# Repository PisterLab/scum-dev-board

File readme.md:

feedback page: https://crystalfree.atlassian.net/wiki/x/AQDGJg

Currently there are three versions of the dev board in this folder
- scum3c_devboard is a KiCad model of the currently in-use board as of October 12th 2020. It might be not 100% accurate to the original: https://github.com/PisterLab/scum-dev-board/blob/master/SCM3C_PCB.pdf
- mccoy is a small 1.675 in X 1.35 in board. It has GPIO pins, an IMU, and battery power
- scum3c_devboard_large is a larger board, supposed to replace the currenly in-use board

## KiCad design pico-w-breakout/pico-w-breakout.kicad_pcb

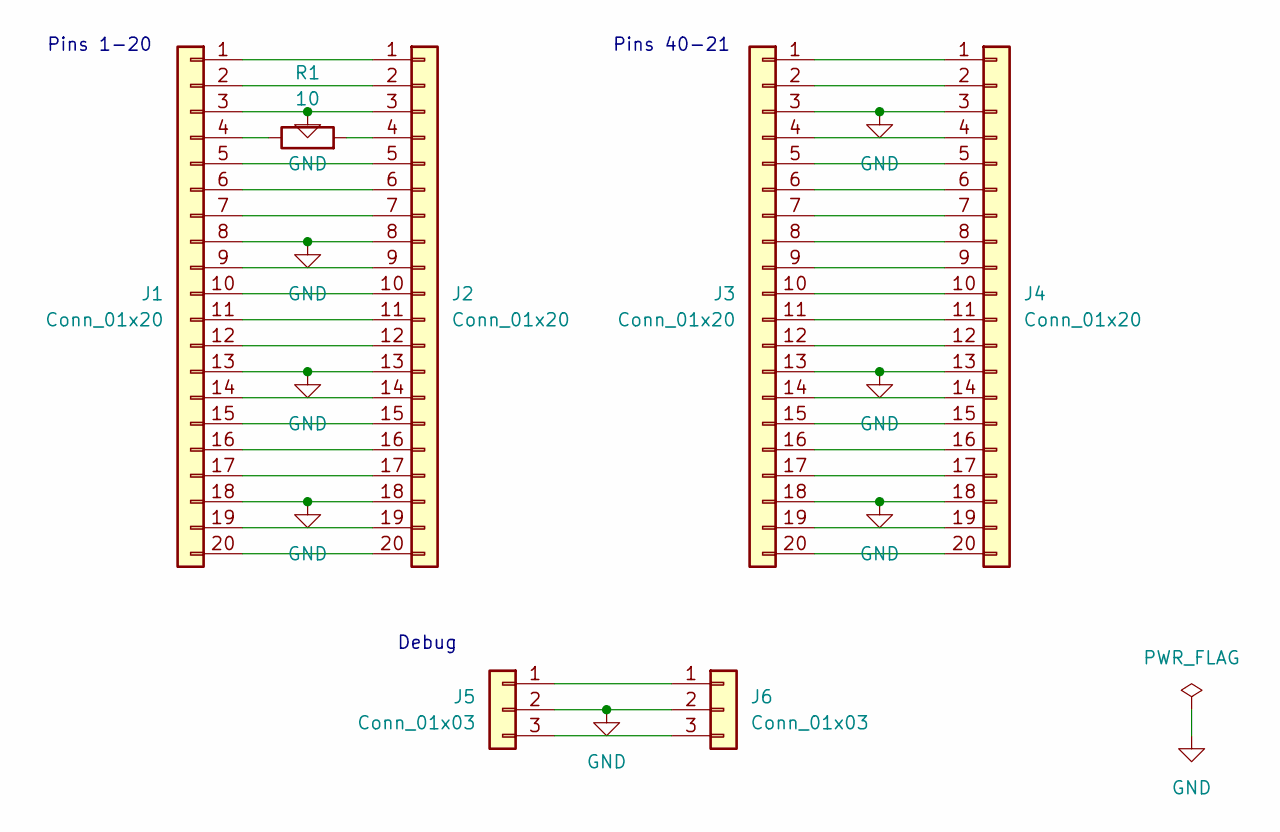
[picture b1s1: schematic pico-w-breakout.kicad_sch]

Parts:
J1, J4: Conn_01x20; PinHeader_1x20_P2.54mm_Vertical
J2, J3: Conn_01x20; PinSocket_1x20_P2.54mm_Vertical
J5: Conn_01x03; PinHeader_1x03_P2.54mm_Vertical
J6: Conn_01x03; PinSocket_1x03_P2.54mm_Vertical
R1: 10; R_0603_1608Metric

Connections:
GND: J1.3, J1.8, J1.13, J1.18, J2.3, J2.8, J2.13, J2.18, J3.3, J3.13, J3.18, J4.3, J4.13, J4.18, J5.2, J6.2
unnamed: J1.1, J2.1
unnamed: J1.2, J2.2
unnamed: J1.4, R1.1
unnamed: J1.5, J2.5
unnamed: J1.6, J2.6
unnamed: J1.7, J2.7
unnamed: J1.9, J2.9
unnamed: J1.10, J2.10
unnamed: J1.11, J2.11
unnamed: J1.12, J2.12
unnamed: J1.14, J2.14
unnamed: J1.15, J2.15
unnamed: J1.16, J2.16
unnamed: J1.17, J2.17
unnamed: J1.19, J2.19
unnamed: J1.20, J2.20
unnamed: J2.4, R1.2
unnamed: J3.1, J4.1
unnamed: J3.2, J4.2
unnamed: J3.4, J4.4
unnamed: J3.5, J4.5
unnamed: J3.6, J4.6
unnamed: J3.7, J4.7
unnamed: J3.8, J4.8
unnamed: J3.9, J4.9
unnamed: J3.10, J4.10
unnamed: J3.11, J4.11
unnamed: J3.12, J4.12
unnamed: J3.14, J4.14
unnamed: J3.15, J4.15
unnamed: J3.16, J4.16
unnamed: J3.17, J4.17
unnamed: J3.19, J4.19
unnamed: J3.20, J4.20
unnamed: J5.1, J6.1
unnamed: J5.3, J6.3

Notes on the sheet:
Pins 40-21
Debug
Pins 1-20

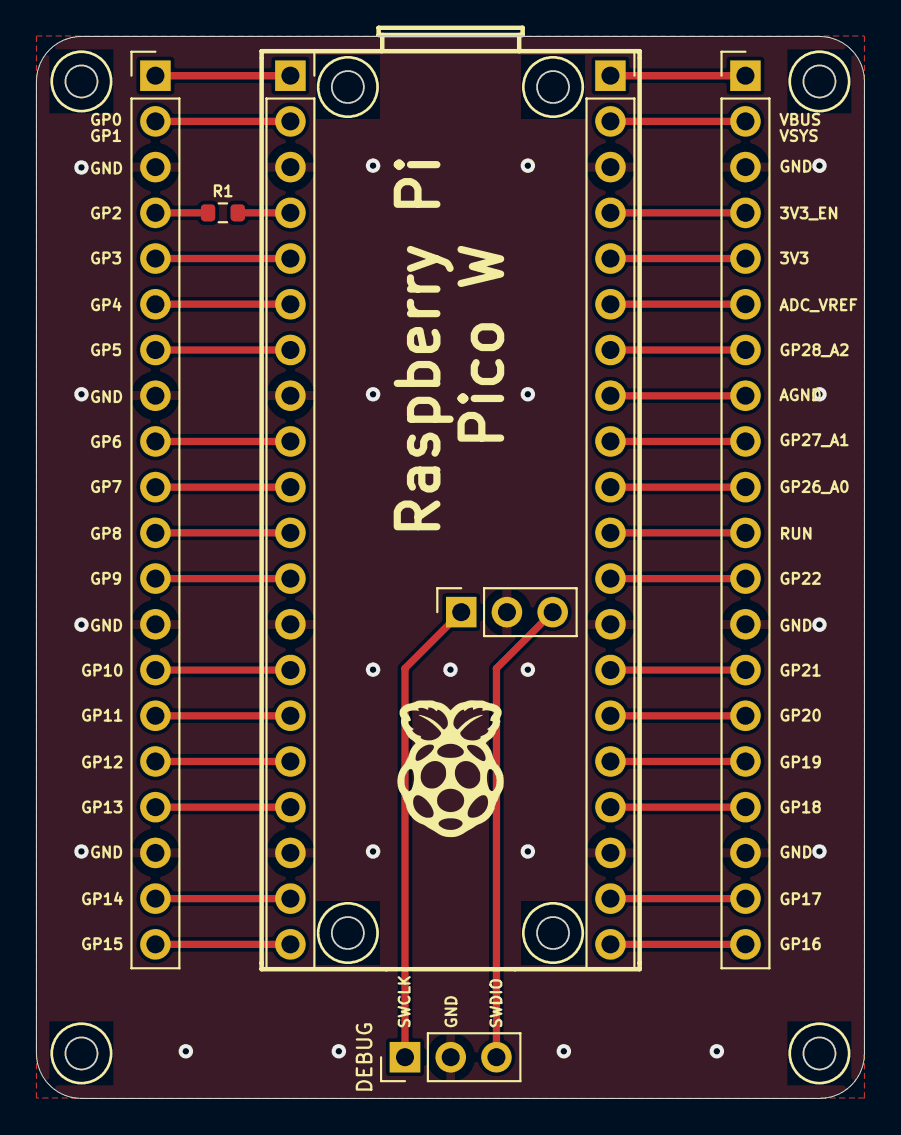
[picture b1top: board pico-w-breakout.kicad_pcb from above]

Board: 2 copper layers, 46.0 x 59.0 mm, 7 parts (0 on the bottom side), 37 nets.

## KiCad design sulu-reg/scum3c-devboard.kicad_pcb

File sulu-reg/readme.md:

# Changelog

### Update 2021.11.23
- Moved GND on 1x10 to match with nRF P4 in reverse orientation

| nRF pin | Sulu pin        |
|---------|-----------------|
| P1.10   | VBAT            |
| P1.11   | NRF_VDDD / HI-Z |
| P1.12   | NRF_GND / HI-Z  |
| P1.13   | HARD_RESET      |
| P1.14   | 3WB_DATA        |
| P1.15   | 3WB_ENB         |
| GND     | GND             |
| P0.02   | 3WB_CLK         |
| P0.26   | RsRx            |
| P0.27   | RsTx            |

### Update 2021.11.19
- Rdded orientation dots for DC-DC converters and IMU
- Replaced 2x5 header with 1x10 header for nRF interface.

### Update 2021.11.04
Replaced DC-DC converter inductor and capacitor footprints to fit with recommended passives from datasheet https://www.ablic.com/en/doc/datasheet/switching_regulator/S85S1A_E.pdf

# images

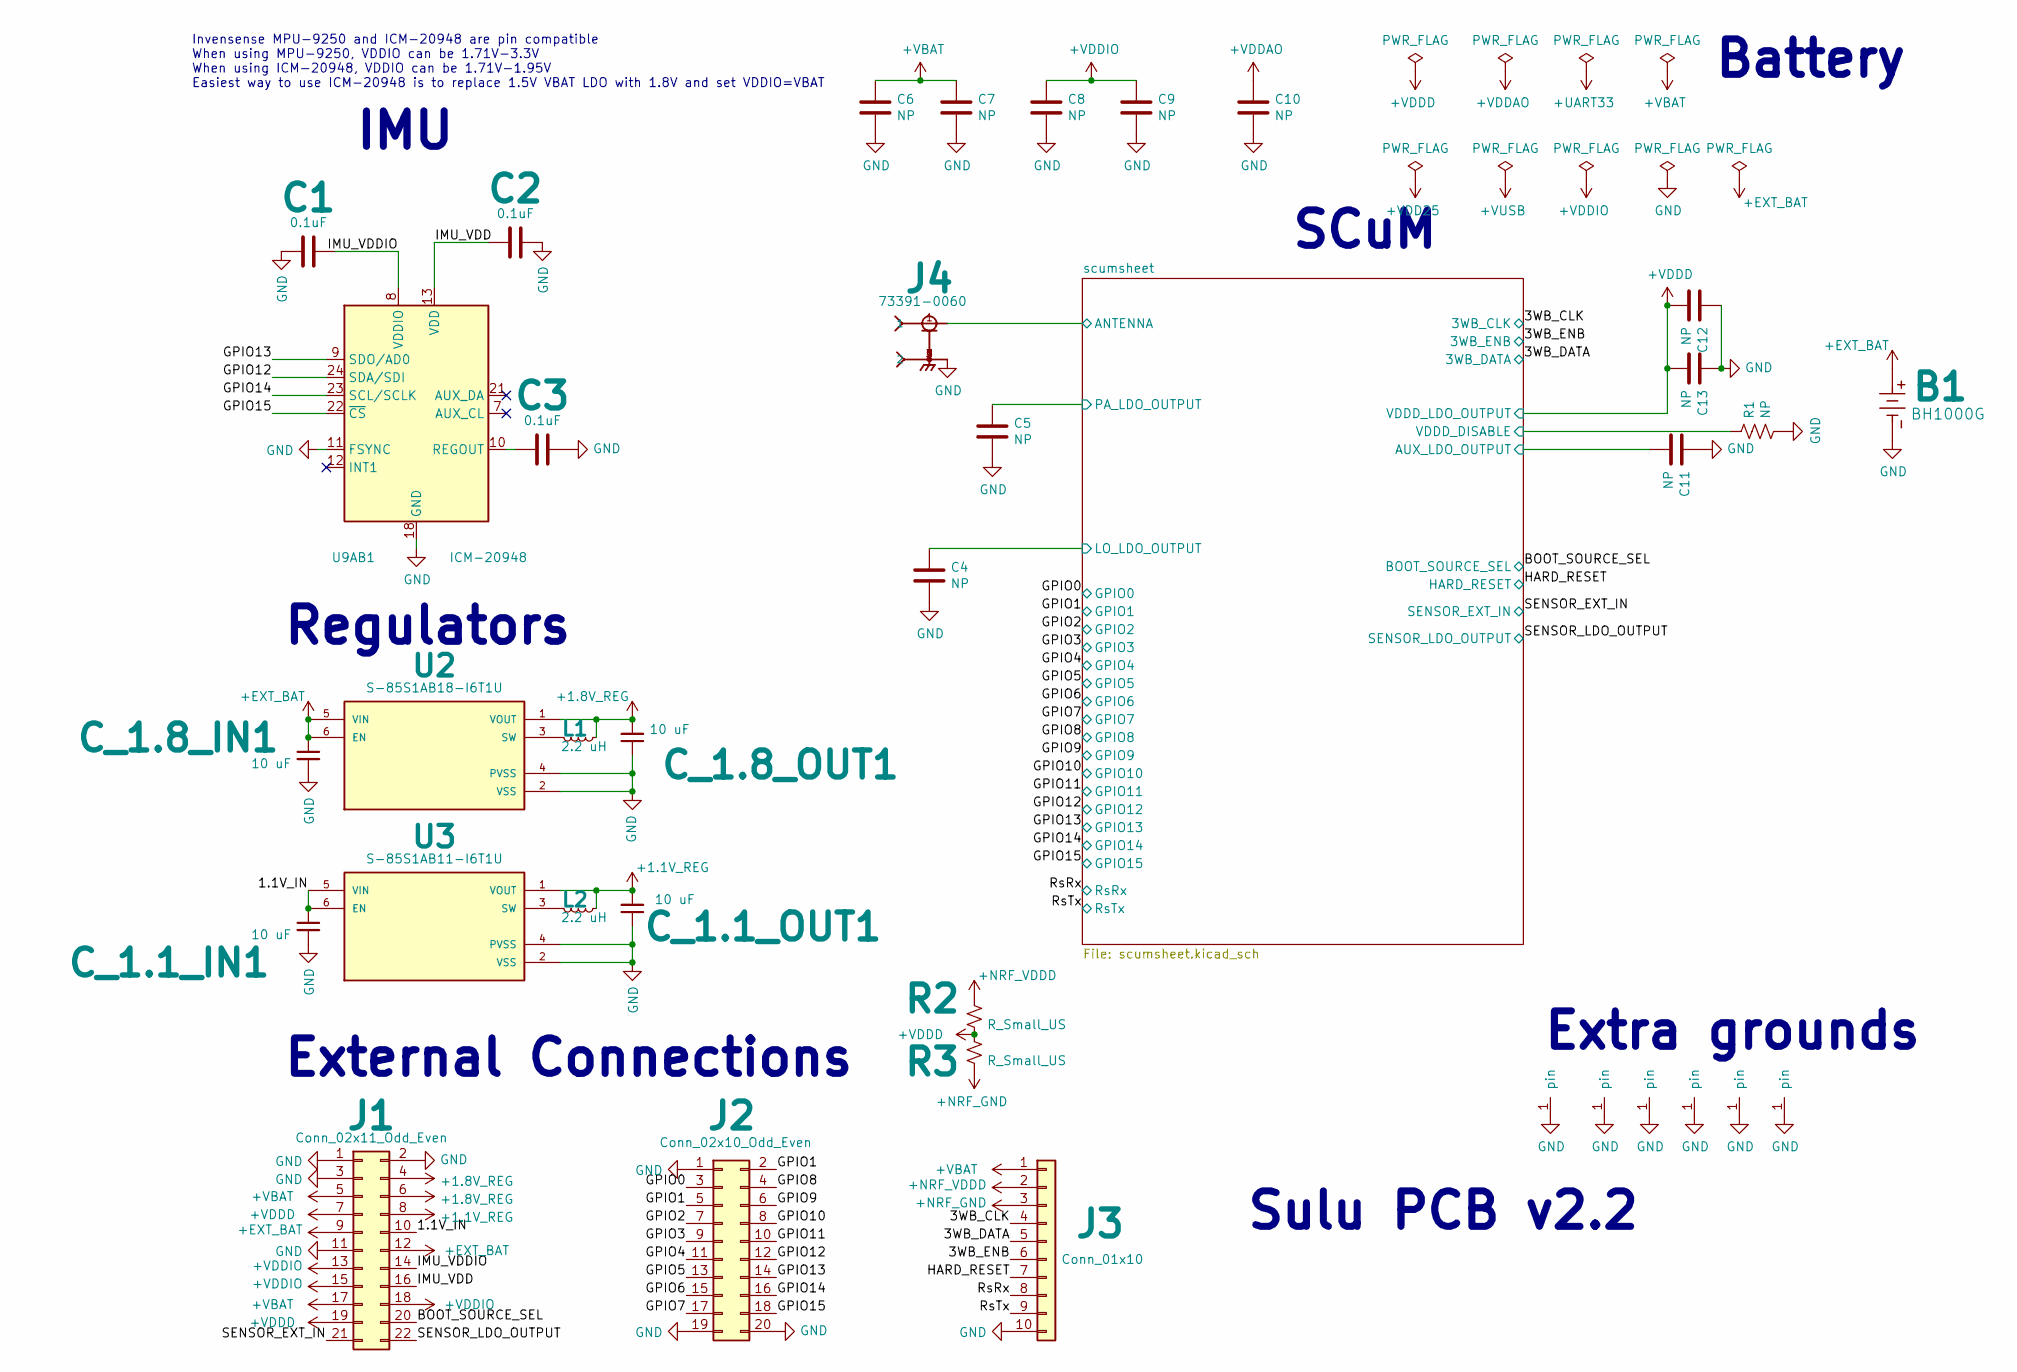
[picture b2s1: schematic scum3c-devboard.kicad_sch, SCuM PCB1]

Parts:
B1: BH1000G
C1, C2, C3: 0.1uF; C_0402_1005Metric
C4, C5, C6, C7, C8, C9, C10, C11, C12, C13: NP; C_0402_1005Metric
C_1.1_IN1, C_1.1_OUT1, C_1.8_IN1, C_1.8_OUT1: 10 uF; C_0402_1005Metric
GND1, GND2, GND3, GND4, GND5, GND6: through_hole
J1: Conn_02x11_Odd_Even; PinHeader_2x11_P2.54mm_Vertical
J2: Conn_02x10_Odd_Even; PinHeader_2x10_P2.54mm_Vertical
J3: Conn_01x10; PinHeader_1x10_P2.54mm_Vertical
J4: 73391-0060; MOLEX_73391-0060
L1, L2: 2.2 uH; L_Wuerth_MAPI-2010
R1: NP; R_0402_1005Metric
R2, R3: R_Small_US; R_0402_1005Metric
U2: S-85S1AB18-I6T1U; SOFL50P180X50-6N; PARTREV 1.4_00
U3: S-85S1AB11-I6T1U; SOFL50P180X50-6N; PARTREV 1.4_00
U9AB1: ICM-20948; InvenSense_QFN-24_3x3mm_P0.4mm

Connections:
+1.1V_REG: C_1.1_OUT1.2, J1.8, L2.1, U3.1 (VOUT)
+1.8V_REG: C_1.8_OUT1.2, J1.4, J1.6, L1.1, U2.1 (VOUT)
+EXT_BAT: B1.2, C_1.8_IN1.1, J1.9, J1.12, U2.5 (VIN), U2.6 (EN)
+NRF_GND: J3.3, R3.2
+NRF_VDDD: J3.2, R2.1
+VBAT: C6.1, C7.1, J1.5, J1.17, J3.1; also elsewhere on the board
+VDDAO: C10.1; also elsewhere on the board
+VDDD: C12.2, C13.2, J1.7, J1.19, R2.2, R3.1; also elsewhere on the board
+VDDIO: C8.1, C9.1, J1.13, J1.15, J1.18; also elsewhere on the board
/1.1V_IN: C_1.1_IN1.1, J1.10, U3.5 (VIN), U3.6 (EN)
/3WB_CLK: J3.4; also elsewhere on the board
/3WB_DATA: J3.5; also elsewhere on the board
/3WB_ENB: J3.6; also elsewhere on the board
/BOOT_SOURCE_SEL: J1.20; also elsewhere on the board
/GPIO0: J2.3; also elsewhere on the board
/GPIO1: J2.2, J2.5; also elsewhere on the board
/GPIO2: J2.7; also elsewhere on the board
/GPIO3: J2.9; also elsewhere on the board
/GPIO4: J2.11; also elsewhere on the board
/GPIO5: J2.13; also elsewhere on the board
/GPIO6: J2.15; also elsewhere on the board
/GPIO7: J2.17; also elsewhere on the board
/GPIO8: J2.4; also elsewhere on the board
/GPIO9: J2.6; also elsewhere on the board
/GPIO10: J2.8; also elsewhere on the board
/GPIO11: J2.10; also elsewhere on the board
/GPIO12: J2.12, U9AB1.24 (SDA/SDI); also elsewhere on the board
/GPIO13: J2.14, U9AB1.9 (SDO/AD0); also elsewhere on the board
/GPIO14: J2.16, U9AB1.23 (SCL/SCLK); also elsewhere on the board
/GPIO15: J2.18, U9AB1.22 (~CS); also elsewhere on the board
/HARD_RESET: J3.7; also elsewhere on the board
/IMU_VDD: C2.1, J1.16, U9AB1.13 (VDD)
/IMU_VDDIO: C1.1, J1.14, U9AB1.8 (VDDIO)
/RsRx: J3.8; also elsewhere on the board
/RsTx: J3.9; also elsewhere on the board
/SENSOR_EXT_IN: J1.21; also elsewhere on the board
/SENSOR_LDO_OUTPUT: J1.22; also elsewhere on the board
/scumsheet/ANTENNA: J4.1; also elsewhere on the board
/scumsheet/AUX_LDO_OUTPUT: C11.2; also elsewhere on the board
/scumsheet/LO_LDO_OUTPUT: C4.1; also elsewhere on the board
/scumsheet/PA_LDO_OUTPUT: C5.1; also elsewhere on the board
/scumsheet/VDDD_DISABLE: R1.1; also elsewhere on the board
GND: B1.1, C1.2, C2.2, C3.2, C4.2, C5.2, C6.2, C7.2, C8.2, C9.2, C10.2, C11.1, C12.1, C13.1, C_1.1_IN1.2, C_1.1_OUT1.1, C_1.8_IN1.2, C_1.8_OUT1.1, GND1.1 (pin), GND2.1 (pin), GND3.1 (pin), GND4.1 (pin), GND5.1 (pin), GND6.1 (pin), J1.1, J1.2, J1.3, J1.11, J2.1, J2.19, J2.20, J3.10, J4.2, J4.3 (2), J4.4 (2), J4.5 (2), R1.2, U2.2 (VSS), U2.4 (PVSS), U3.2 (VSS), U3.4 (PVSS), U9AB1.11 (FSYNC), U9AB1.18 (GND), U9AB1.20 (GND); also elsewhere on the board
unnamed: L1.2, U2.3 (SW)
unnamed: L2.2, U3.3 (SW)
unnamed: C3.1, U9AB1.10 (REGOUT)

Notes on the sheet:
SCuM
Extra grounds
Sulu PCB v2.2
Invensense MPU-9250 and ICM-20948 are pin compatible When using MPU-9250, VDDIO can be 1.71V-3.3V When using ICM-20948, VDDIO can be 1.71V-1.95V Easiest way to use ICM-20948 is to replace 1.5V VBAT LDO with 1.8V and set VDDIO=VBAT
External Connections
Regulators
Battery
IMU

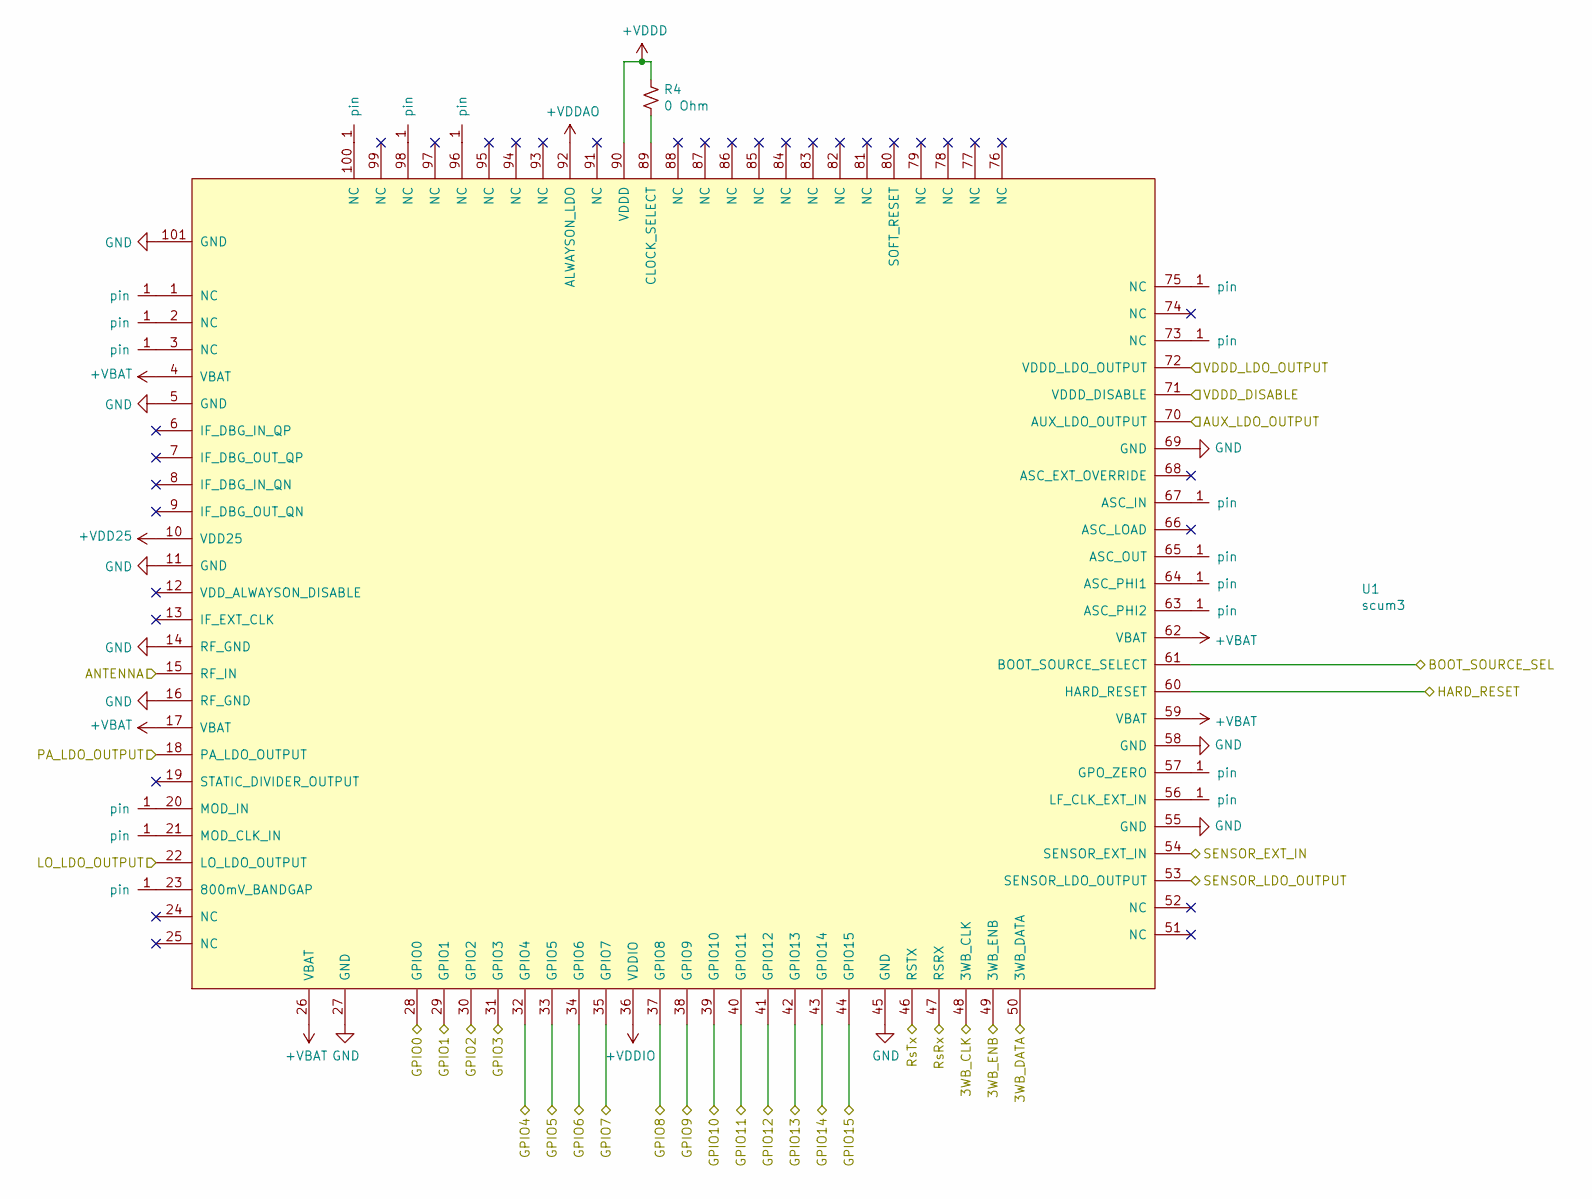
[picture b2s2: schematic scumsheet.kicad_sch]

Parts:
J5, J6, J7, J8, J9, J10, J11, J12, J13, J14, J15, J16, J17, J18, J19, J20, J21: through_hole
R4: 0 Ohm; R_0402_1005Metric
U1: scum3; QFN-100_EP_12x12_Pitch0.4mm_Margin0.25mm

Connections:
+VBAT: U1.4 (VBAT), U1.17 (VBAT), U1.26 (VBAT), U1.59 (VBAT), U1.62 (VBAT); also elsewhere on the board
+VDD25: U1.10 (VDD25)
+VDDAO: U1.92 (ALWAYSON_LDO); also elsewhere on the board
+VDDD: R4.1, U1.72 (VDDD_LDO_OUTPUT), U1.90 (VDDD); also elsewhere on the board
+VDDIO: U1.36 (VDDIO); also elsewhere on the board
/3WB_CLK: U1.48 (3WB_CLK); also elsewhere on the board
/3WB_DATA: U1.50 (3WB_DATA); also elsewhere on the board
/3WB_ENB: U1.49 (3WB_ENB); also elsewhere on the board
/BOOT_SOURCE_SEL: U1.61 (BOOT_SOURCE_SELECT); also elsewhere on the board
/GPIO0: U1.28 (GPIO0); also elsewhere on the board
/GPIO1: U1.29 (GPIO1); also elsewhere on the board
/GPIO2: U1.30 (GPIO2); also elsewhere on the board
/GPIO3: U1.31 (GPIO3); also elsewhere on the board
/GPIO4: U1.32 (GPIO4); also elsewhere on the board
/GPIO5: U1.33 (GPIO5); also elsewhere on the board
/GPIO6: U1.34 (GPIO6); also elsewhere on the board
/GPIO7: U1.35 (GPIO7); also elsewhere on the board
/GPIO8: U1.37 (GPIO8); also elsewhere on the board
/GPIO9: U1.38 (GPIO9); also elsewhere on the board
/GPIO10: U1.39 (GPIO10); also elsewhere on the board
/GPIO11: U1.40 (GPIO11); also elsewhere on the board
/GPIO12: U1.41 (GPIO12); also elsewhere on the board
/GPIO13: U1.42 (GPIO13); also elsewhere on the board
/GPIO14: U1.43 (GPIO14); also elsewhere on the board
/GPIO15: U1.44 (GPIO15); also elsewhere on the board
/HARD_RESET: U1.60 (HARD_RESET); also elsewhere on the board
/RsRx: U1.47 (RSRX); also elsewhere on the board
/RsTx: U1.46 (RSTX); also elsewhere on the board
/SENSOR_EXT_IN: U1.54 (SENSOR_EXT_IN); also elsewhere on the board
/SENSOR_LDO_OUTPUT: U1.53 (SENSOR_LDO_OUTPUT); also elsewhere on the board
/scumsheet/ANTENNA: U1.15 (RF_IN); also elsewhere on the board
/scumsheet/AUX_LDO_OUTPUT: U1.70 (AUX_LDO_OUTPUT); also elsewhere on the board
/scumsheet/LO_LDO_OUTPUT: U1.22 (LO_LDO_OUTPUT); also elsewhere on the board
/scumsheet/PA_LDO_OUTPUT: U1.18 (PA_LDO_OUTPUT); also elsewhere on the board
/scumsheet/VDDD_DISABLE: U1.71 (VDDD_DISABLE); also elsewhere on the board
GND: U1.5 (GND), U1.11 (GND), U1.14 (RF_GND), U1.16 (RF_GND), U1.27 (GND), U1.45 (GND), U1.55 (GND), U1.58 (GND), U1.69 (GND), U1.101 (GND); also elsewhere on the board
unnamed: J5.1 (pin), U1.73 (NC)
unnamed: J6.1 (pin), U1.1 (NC)
unnamed: J7.1 (pin), U1.2 (NC)
unnamed: J8.1 (pin), U1.3 (NC)
unnamed: J9.1 (pin), U1.63 (ASC_PHI2)
unnamed: J10.1 (pin), U1.64 (ASC_PHI1)
unnamed: J11.1 (pin), U1.20 (MOD_IN)
unnamed: J12.1 (pin), U1.21 (MOD_CLK_IN)
unnamed: J13.1 (pin), U1.23 (800mV_BANDGAP)
unnamed: J14.1 (pin), U1.100 (NC)
unnamed: J15.1 (pin), U1.67 (ASC_IN)
unnamed: J16.1 (pin), U1.65 (ASC_OUT)
unnamed: J17.1 (pin), U1.56 (LF_CLK_EXT_IN)
unnamed: J18.1 (pin), U1.98 (NC)
unnamed: J19.1 (pin), U1.96 (NC)
unnamed: J20.1 (pin), U1.75 (NC)
unnamed: J21.1 (pin), U1.57 (GPO_ZERO)
unnamed: R4.2, U1.89 (CLOCK_SELECT)

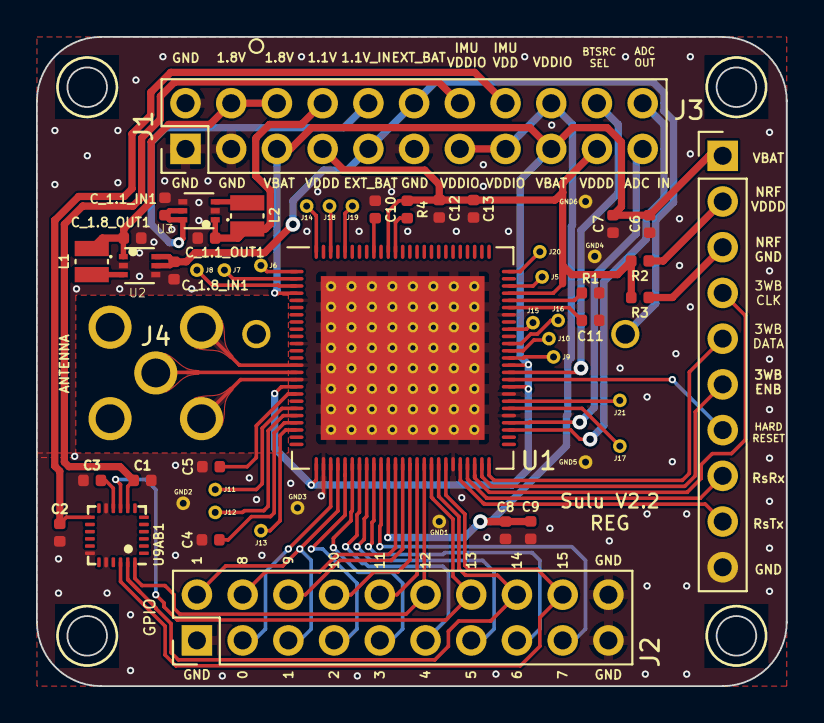
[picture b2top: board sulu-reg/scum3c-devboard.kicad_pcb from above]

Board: 2 copper layers, 41.7 x 36.1 mm, 55 parts (1 on the bottom side), 64 nets.

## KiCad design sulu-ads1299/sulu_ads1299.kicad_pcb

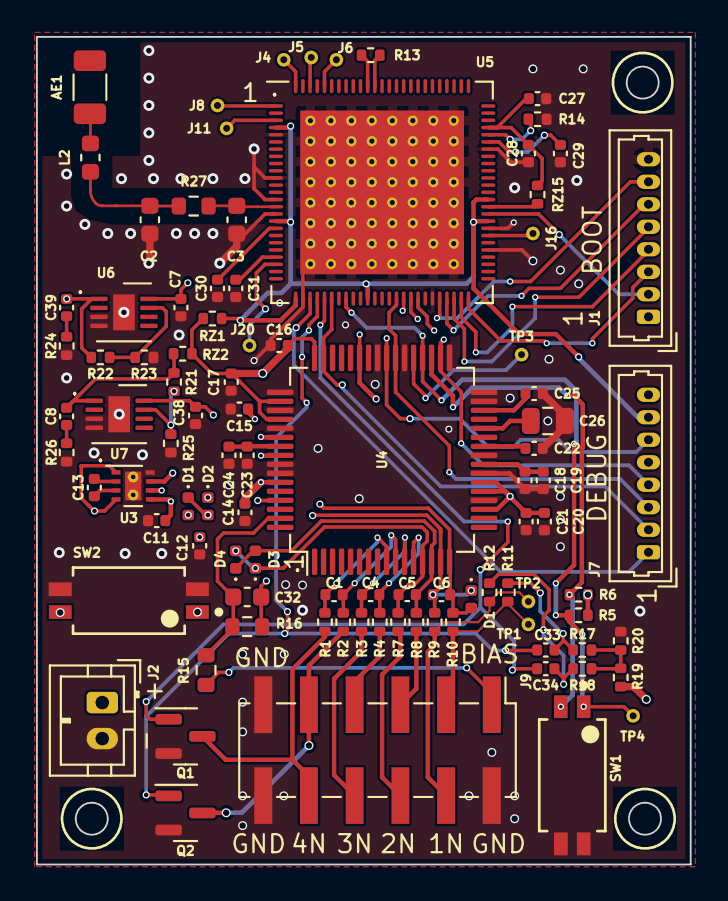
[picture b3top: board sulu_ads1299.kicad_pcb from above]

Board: 6 copper layers, 36.3 x 46.0 mm, 95 parts (1 on the bottom side), 75 nets.

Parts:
AE1: RFANT3216120A5T; C_1206_3216Metric
C1, C4, C5, C6, C33, C34: 3.3 uF; C_0402_1005Metric
C2: 0.5 pF; C_0603_1608Metric
C3: NP; C_0603_1608Metric
C7, C13, C14, C17, C20, C22, C23, C25, C38: 1 uF; C_0402_1005Metric
C8, C39: 4.7 uF; C_0402_1005Metric
C11, C12, C19: 10 uF; C_0402_1005Metric
C15, C16, C18, C21, C24: 0.1 uF; C_0402_1005Metric
C26: 100 uF; C_0805_2012Metric
C27, C28, C29, C30, C31: NP; C_0402_1005Metric
C32: 0.01uF; C_0603_1608Metric
D1, D1#2, D2, D3, D4: GDZ5V1LP3-7; D_0402_1005Metric
J1, J7: Conn_01x08; Molex_PicoBlade_53047-0810_1x08_P1.25mm_Vertical
J2: Conn_01x02; JST_PH_B2B-PH-K_1x02_P2.00mm_Vertical
J4, J5, J6, J8, J11, J16, J20: through_hole
J9: Conn_02x06_Odd_Even; PinHeader_2x06_P2.54mm_Vertical_SMD
L2: 6.7 nH; L_0603_1608Metric
Q1, Q2: BSS138; SOT-23
R1, R2, R3, R4, R7, R8, R9, R10: 200; R_0402_1005Metric
R5, R6: 10K; R_0402_1005Metric
R11, R12: 0; R_0402_1005Metric
R13: 0 Ohm; R_0402_1005Metric
R14: NP; R_0402_1005Metric
R15: 4.99K; R_0603_1608Metric
R16: 392K; R_0603_1608Metric
R17, R18, R19, R20, R23, R25: 100K; R_0402_1005Metric
R21, R22: 46K; R_0402_1005Metric
R24, R26: 1; R_0402_1005Metric
R27: 0; R_0603_1608Metric
RZ1, RZ15: 0 Ohm; R_0402_1005Metric
RZ2: NP; R_0402_1005Metric
SW1, SW2: SW_DIP_x02; CK_Components-TDA02H0SB1-MFG
TP1, TP2, TP3, TP4: TestPoint; through_hole
U3: LM2775DSG; WSON-8-1EP_2x2mm_P0.5mm_EP0.9x1.6mm_ThermalVias
U4: ADS1299_TQFP-64; TQFP-64_10x10mm_P0.5mm
U5: scum3; QFN-100_EP_12x12_Pitch0.4mm_Margin0.25mm
U6, U7: LP2951-5.0_WSON; WSON-8-1EP_3x3mm_P0.5mm_EP1.2x2mm

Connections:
+5V_REG: C12.1, C14.1, C15.1, C20.1, C21.1, R19.1, U3.6 (VOUT), U4.19 (AVDD), U4.21 (AVDD), U4.22 (AVDD), U4.54 (AVDD1), U4.56 (AVDD), U4.59 (AVDD)
+EXT_BAT: J1.1, J2.1, SW2.1
/3WB_CLK: J1.5, U5.48 (3WB_CLK)
/3WB_DATA: J1.3, U5.50 (3WB_DATA)
/3WB_ENB: J1.4, U5.49 (3WB_ENB)
/+1.8V_ADS: C16.1, C17.1, J7.8, R5.1, R6.1, RZ1.1, RZ2.2, U4.48 (DVDD), U4.50 (DVDD), U4.52 (CLKSEL)
/+1.8V_BACKUP: C8.2, R21.2, RZ2.1, U7.1 (OUT)
/+1.8V_SCUM: C39.2, J7.7, R22.2, RZ1.2, U5.4 (VBAT), U5.17 (VBAT), U5.26 (VBAT), U5.36 (VDDIO), U5.59 (VBAT), U5.62 (VBAT), U6.1 (OUT)
/ADS1299/BIASINV: C32.1, R16.1, U4.61 (BIASINV)
/ADS1299/BIASOUT: C32.2, R15.2, R16.2, U4.63 (BIASOUT)
/ADS1299/VCAP1: C26.1, U4.28 (VCAP1)
/ADS1299/VCAP2: C25.1, U4.30 (VCAP2)
/ADS1299/VCAP3: C23.1, C24.1, U4.55 (VCAP3)
/ADS1299/VCAP4: C22.1, U4.26 (VCAP4)
/ADS1299/VREFP: C18.1, C19.1, U4.24 (VREFP)
/ADS_BIAS_ELEC: J9.1, R15.1
/ADS_IN1N: C6.1, D1.1 (K), D1#2.1 (K), D2.2 (A), R9.2, U4.15 (IN1N)
/ADS_IN1N_CONN: J9.4, R9.1, R12.2, TP2.1
/ADS_IN1P: C6.2, D1.2 (A), D1#2.2 (A), D2.1 (K), R10.2, U4.16 (IN1P)
/ADS_IN1P_CONN: J9.3, R10.1, R11.2, TP1.1
/ADS_IN2N: C5.1, D3.1 (K), D4.2 (A), R7.2, U4.13 (IN2N)
/ADS_IN2N_CONN: J9.6, R7.1
/ADS_IN2P: C5.2, D3.2 (A), D4.1 (K), R8.2, U4.14 (IN2P)
/ADS_IN2P_CONN: J9.5, R8.1
/ADS_IN3N: C4.1, R3.2, U4.11 (IN3N)
/ADS_IN3N_CONN: J9.8, R3.1
/ADS_IN3P: C4.2, R4.2, U4.12 (IN3P)
/ADS_IN3P_CONN: J9.7, R4.1
/ADS_IN4N: C1.1, R1.2, U4.9 (IN4N)
/ADS_IN4N_CONN: J9.10, Q1.3 (D), R1.1
/ADS_IN4P: C1.2, R2.2, U4.10 (IN4P)
/ADS_IN4P_CONN: J9.9, Q2.3 (D), R2.1
/EXT_BAT_SW: C7.1, C11.1, C38.1, SW2.4, U3.1 (PFM), U3.4 (OUTDIS), U3.5 (EN), U3.7 (VIN), U6.8 (IN), U7.8 (IN)
/HARD_RESET: J1.2, U5.60 (HARD_RESET)
/RsRx: J1.6, U5.47 (RSRX)
/RsTx: J1.7, U5.46 (RSTX)
/SCUM_GPIO0: J7.1, U5.28 (GPIO0)
/SCUM_GPIO1: C33.2, Q2.1 (G), U5.29 (GPIO1)
/SCUM_GPIO2: C34.2, Q1.1 (G), U5.30 (GPIO2)
/SCUM_GPIO3: J7.2, U4.47 (~DRDY), U5.31 (GPIO3)
/SCUM_GPIO5: R5.2, SW1.1, TP4.1, U4.36 (~RESET), U5.33 (GPIO5)
/SCUM_GPIO11: J7.3, U4.39 (~CS), U5.40 (GPIO11)
/SCUM_GPIO12: J7.4, U4.34 (DIN), U5.41 (GPIO12)
/SCUM_GPIO13: J7.5, U4.43 (DOUT), U5.42 (GPIO13)
/SCUM_GPIO14: J7.6, U4.40 (SCLK), U5.43 (GPIO14)
/SCuM-3C/+1.1V_REG: C27.1, C28.1, RZ15.2, U5.72 (VDDD_LDO_OUTPUT)
/SCuM-3C/ANTENNA: C3.2, R27.2, U5.15 (RF_IN)
/SELF_TEST_BIAS: R17.2, R18.1, R19.2, R20.1
/SELF_TEST_N: C34.1, R12.1, R18.2
/SELF_TEST_P: C33.1, R11.1, R17.1
/~ADS_PWDN: R6.2, SW1.2, U4.35 (~PWDN)
GND: C2.1, C3.1, C7.2, C11.2, C12.2, C14.2, C15.2, C16.2, C17.2, C18.2, C19.2, C20.2, C21.2, C22.2, C23.2, C24.2, C25.2, C26.2, C27.2, C28.2, C29.2, C30.2, C31.2, C38.2, J1.8, J2.2, J9.2, J9.11, J9.12, Q1.2 (S), Q2.2 (S), R14.2, R20.2, R23.1, R24.1, R25.1, R26.1, SW1.3, SW1.4, SW2.2, SW2.3, U3.8 (GND), U3.9 (GND), U4.20 (AVSS), U4.23 (AVSS), U4.25 (VREFN), U4.31 (RESV1), U4.32 (AVSS), U4.33 (DGND), U4.38 (START), U4.41 (DAISY_IN), U4.49 (DGND), U4.51 (DGND), U4.53 (AVSS1), U4.57 (AVSS), U4.58 (AVSS), U5.5 (GND), U5.11 (GND), U5.14 (RF_GND), U5.16 (RF_GND), U5.27 (GND), U5.45 (GND), U5.55 (GND), U5.58 (GND), U5.69 (GND), U5.101 (GND), U6.3 (SHUTDOWN), U6.4 (GND), U6.9 (EP), U7.3 (SHUTDOWN), U7.4 (GND), U7.9 (EP)
unnamed: AE1.1 (FEED), L2.2
unnamed: C2.2, L2.1, R27.1
unnamed: C8.1, R26.2
unnamed: C39.1, R24.2
unnamed: J4.1 (pin), U5.100 (NC)
unnamed: J5.1 (pin), U5.98 (NC)
unnamed: J6.1 (pin), U5.96 (NC)
unnamed: J8.1 (pin), U5.1 (NC)
unnamed: J11.1 (pin), U5.3 (NC)
unnamed: J16.1 (pin), U5.57 (GPO_ZERO)
unnamed: J20.1 (pin), U5.23 (800mV_BANDGAP)
unnamed: C13.1, U3.3 (C1+)
unnamed: C13.2, U3.2 (C1-)
unnamed: TP3.1, U4.37 (CLK)
unnamed: C29.1, U5.70 (AUX_LDO_OUTPUT)
unnamed: RZ15.1, U5.61 (BOOT_SOURCE_SELECT)
unnamed: R13.2, U5.89 (CLOCK_SELECT)
unnamed: C31.1, U5.22 (LO_LDO_OUTPUT)
unnamed: C30.1, U5.18 (PA_LDO_OUTPUT)
unnamed: R13.1, U5.90 (VDDD)
unnamed: R14.1, U5.71 (VDDD_DISABLE)
unnamed: R22.1, R23.2, U6.7 (FEEDBACK)
unnamed: R21.1, R25.2, U7.7 (FEEDBACK)

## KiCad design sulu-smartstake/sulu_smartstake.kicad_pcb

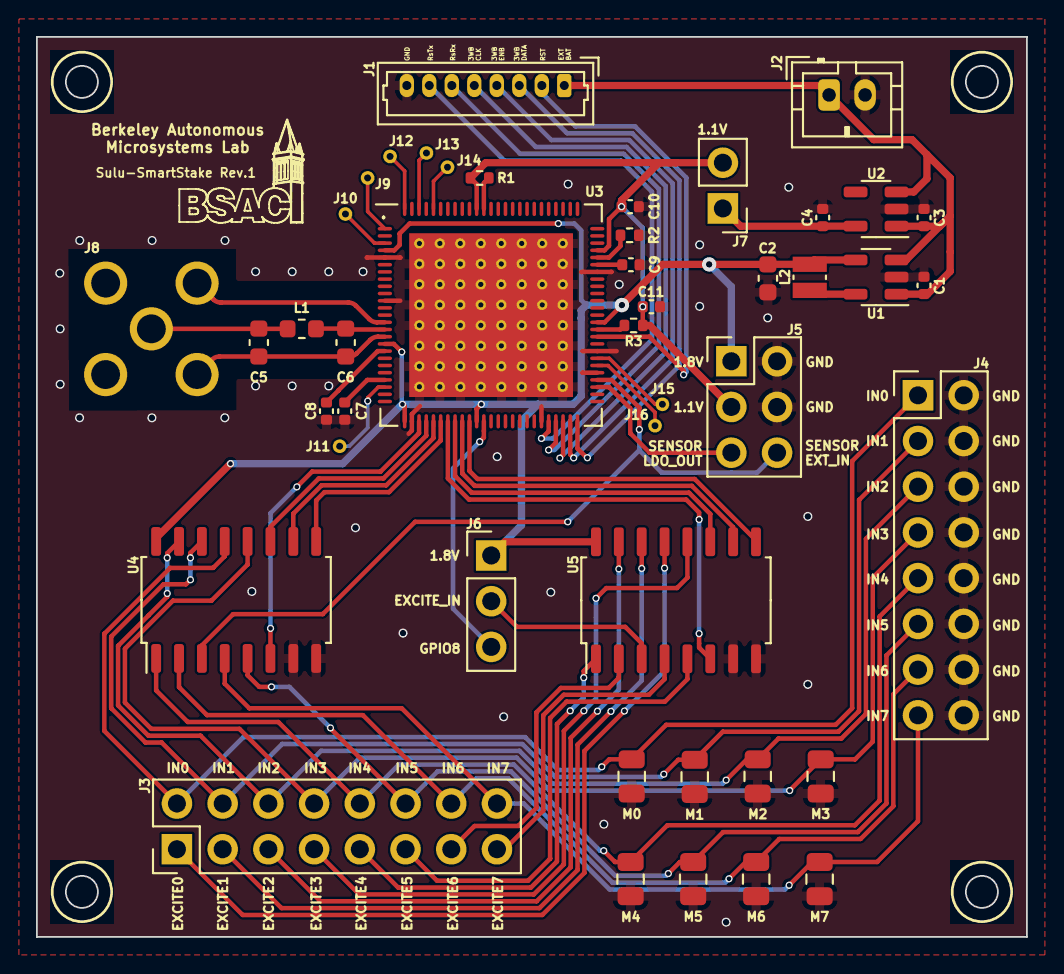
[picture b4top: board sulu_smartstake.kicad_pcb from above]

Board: 2 copper layers, 55.0 x 50.0 mm, 45 parts (0 on the bottom side), 56 nets.

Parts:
C1: 4.7 uF; C_0402_1005Metric
C2: 22 uF; C_0603_1608Metric
C3, C4: 0.1 uF; C_0402_1005Metric
C5, C6: NP; C_0603_1608Metric
C7, C8, C9, C10, C11: NP; C_0402_1005Metric
J1: Conn_01x08; Molex_PicoBlade_53047-0810_1x08_P1.25mm_Vertical
J2: Conn_01x02; JST_PH_B2B-PH-K_1x02_P2.00mm_Vertical
J3, J4: Conn_02x08_Odd_Even; PinHeader_2x08_P2.54mm_Vertical
J5: Conn_02x03_Odd_Even; PinHeader_2x03_P2.54mm_Vertical
J6: Conn_01x03; PinHeader_1x03_P2.54mm_Vertical
J7: Conn_01x02; PinHeader_1x02_P2.54mm_Vertical
J8: 73391-0060; MOLEX_73391-0060
J9, J10, J11, J12, J13, J14, J15, J16: through_hole
L1: NP; L_0603_1608Metric
L2: 4.7 uH; L_Wuerth_MAPI-2010
M0, M1, M2, M3, M4, M5, M6, M7: NP; C_0805_2012Metric
R1, R3: 0 Ohm; R_0402_1005Metric
R2: NP; R_0402_1005Metric
U1: TPS62222DDCT; SOT-23-5
U2: TLV71311PDBV; SOT-23-5
U3: scum3; QFN-100_EP_12x12_Pitch0.4mm_Margin0.25mm
U4, U5: SN74LV4051ADR; SOIC-16_4.55x10.3mm_P1.27mm

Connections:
+1.1V_REG: C4.1, J7.1, U2.5 (OUT)
+1.8V_REG: C2.2, J5.1, J6.1, L2.2, U1.4 (FB), U3.4 (VBAT), U3.17 (VBAT), U3.26 (VBAT), U3.36 (VDDIO), U3.62 (VBAT), U4.16 (VDD), U5.16 (VDD)
+EXT_BAT: C1.1, C3.1, J1.1, J2.1, U1.1 (VI), U1.3 (EN), U2.1 (IN), U2.3 (EN)
/3WB_CLK: J1.5, U3.48 (3WB_CLK)
/3WB_DATA: J1.3, U3.50 (3WB_DATA)
/3WB_ENB: J1.4, U3.49 (3WB_ENB)
/+1.1V_IN: C10.1, C11.1, J5.3, J7.2, R1.1, R3.2, U3.72 (VDDD_LDO_OUTPUT), U3.90 (VDDD)
/EXCITE_IN: J6.2, U5.3 (X)
/HARD_RESET: J1.2, U3.60 (HARD_RESET)
/RsRx: J1.6, U3.47 (RSRX)
/RsTx: J1.7, U3.46 (RSTX)
/SCUM_GPIO0: U3.28 (GPIO0), U4.6 (Inh)
/SCUM_GPIO1: U3.29 (GPIO1), U4.11 (A)
/SCUM_GPIO2: U3.30 (GPIO2), U4.10 (B)
/SCUM_GPIO3: U3.31 (GPIO3), U4.9 (C)
/SCUM_GPIO4: U3.32 (GPIO4), U5.6 (Inh)
/SCUM_GPIO5: U3.33 (GPIO5), U5.11 (A)
/SCUM_GPIO6: U3.34 (GPIO6), U5.10 (B)
/SCUM_GPIO7: U3.35 (GPIO7), U5.9 (C)
/SCUM_GPIO8: J6.3, U3.37 (GPIO8)
/SCuM-3C/ANTENNA: C6.2, L1.2, U3.15 (RF_IN)
/SENSOR_EXCITE0: J3.1, U5.13 (X0)
/SENSOR_EXCITE1: J3.3, U5.14 (X1)
/SENSOR_EXCITE2: J3.5, U5.15 (X2)
/SENSOR_EXCITE3: J3.7, U5.12 (X3)
/SENSOR_EXCITE4: J3.9, U5.1 (X4)
/SENSOR_EXCITE5: J3.11, U5.5 (X5)
/SENSOR_EXCITE6: J3.13, U5.2 (X6)
/SENSOR_EXCITE7: J3.15, U5.4 (X7)
/SENSOR_EXT_IN: J5.6, U3.54 (SENSOR_EXT_IN), U4.3 (X)
/SENSOR_IN0: J3.2, J4.1, M0.2, U4.13 (X0)
/SENSOR_IN1: J3.4, J4.3, M1.2, U4.14 (X1)
/SENSOR_IN2: J3.6, J4.5, M2.2, U4.15 (X2)
/SENSOR_IN3: J3.8, J4.7, M3.2, U4.12 (X3)
/SENSOR_IN4: J3.10, J4.9, M4.2, U4.1 (X4)
/SENSOR_IN5: J3.12, J4.11, M5.2, U4.5 (X5)
/SENSOR_IN6: J3.14, J4.13, M6.2, U4.2 (X6)
/SENSOR_IN7: J3.16, J4.15, M7.2, U4.4 (X7)
/SENSOR_LDO_OUTPUT: J5.5, U3.53 (SENSOR_LDO_OUTPUT)
GND: C1.2, C2.1, C3.2, C4.2, C5.1, C6.1, C7.2, C8.2, C9.2, C10.2, C11.2, J1.8, J2.2, J4.2, J4.4, J4.6, J4.8, J4.10, J4.12, J4.14, J4.16, J5.2, J5.4, J8.2, J8.3 (2), J8.4 (2), J8.5 (2), M0.1, M1.1, M2.1, M3.1, M4.1, M5.1, M6.1, M7.1, R2.2, U1.2 (GND), U2.2 (GND), U3.5 (GND), U3.11 (GND), U3.14 (RF_GND), U3.16 (RF_GND), U3.27 (GND), U3.45 (GND), U3.55 (GND), U3.58 (GND), U3.69 (GND), U3.101 (GND), U4.7 (VEE), U4.8 (VSS), U5.7 (VEE), U5.8 (VSS)
unnamed: C5.2, J8.1, L1.1
unnamed: J9.1 (pin), U3.1 (NC)
unnamed: J10.1 (pin), U3.3 (NC)
unnamed: J11.1 (pin), U3.23 (800mV_BANDGAP)
unnamed: J12.1 (pin), U3.100 (NC)
unnamed: J13.1 (pin), U3.98 (NC)
unnamed: J14.1 (pin), U3.96 (NC)
unnamed: J15.1 (pin), U3.57 (GPO_ZERO)
unnamed: J16.1 (pin), U3.56 (LF_CLK_EXT_IN)
unnamed: L2.1, U1.5 (SW)
unnamed: C9.1, U3.70 (AUX_LDO_OUTPUT)
unnamed: R3.1, U3.61 (BOOT_SOURCE_SELECT)
unnamed: R1.2, U3.89 (CLOCK_SELECT)
unnamed: C7.1, U3.22 (LO_LDO_OUTPUT)
unnamed: C8.1, U3.18 (PA_LDO_OUTPUT)
unnamed: R2.1, U3.71 (VDDD_DISABLE)

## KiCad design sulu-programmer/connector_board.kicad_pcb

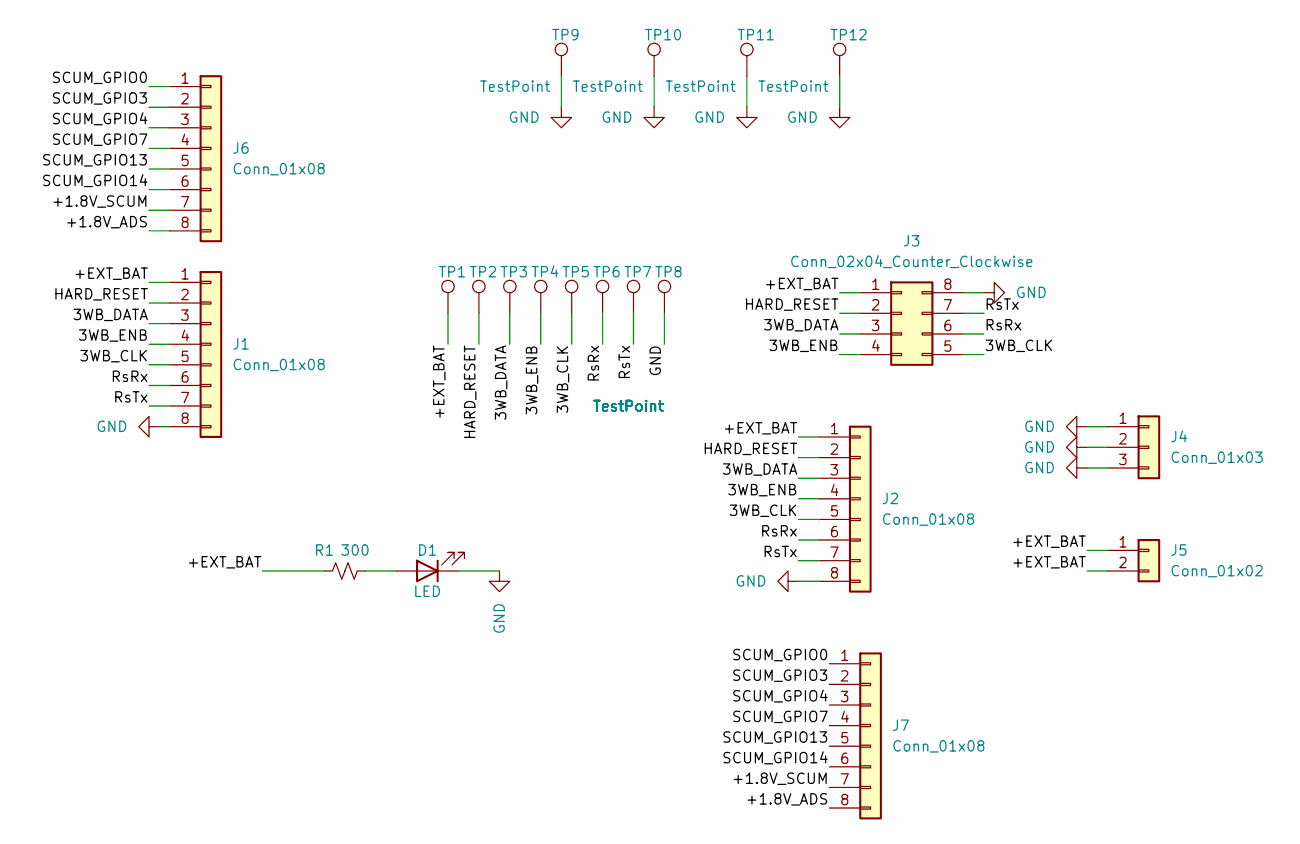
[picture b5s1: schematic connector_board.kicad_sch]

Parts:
D1: LED; LED_0805_2012Metric
J1, J6: Conn_01x08; Molex_PicoBlade_53047-0810_1x08_P1.25mm_Vertical
J2, J7: Conn_01x08; PinHeader_1x08_P2.54mm_Vertical
J3: Conn_02x04_Counter_Clockwise; PinHeader_2x04_P2.54mm_Vertical
J4: Conn_01x03; PinHeader_1x03_P2.54mm_Vertical
J5: Conn_01x02; PinHeader_1x02_P2.54mm_Vertical
R1: 300; R_0402_1005Metric
TP1, TP2, TP3, TP4, TP5, TP6, TP7, TP8: TestPoint; TestPoint_THTPad_1.0x1.0mm_Drill0.5mm
TP9, TP10, TP11, TP12: TestPoint; TestPoint_Keystone_5010-5014_Multipurpose

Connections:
/3WB_CLK: J1.5, J2.5, J3.5, TP5.1
/3WB_DATA: J1.3, J2.3, J3.3, TP3.1
/3WB_ENB: J1.4, J2.4, J3.4, TP4.1
/+1.8V_ADS: J6.8, J7.8
/+1.8V_SCUM: J6.7, J7.7
/+EXT_BAT: J1.1, J2.1, J3.1, J5.1, J5.2, R1.1, TP1.1
/HARD_RESET: J1.2, J2.2, J3.2, TP2.1
/RsRx: J1.6, J2.6, J3.6, TP6.1
/RsTx: J1.7, J2.7, J3.7, TP7.1
/SCUM_GPIO0: J6.1, J7.1
/SCUM_GPIO3: J6.2, J7.2
/SCUM_GPIO4: J6.3, J7.3
/SCUM_GPIO7: J6.4, J7.4
/SCUM_GPIO13: J6.5, J7.5
/SCUM_GPIO14: J6.6, J7.6
GND: D1.1 (K), J1.8, J2.8, J3.8, J4.1, J4.2, J4.3, TP8.1, TP9.1, TP10.1, TP11.1, TP12.1
unnamed: D1.2 (A), R1.2

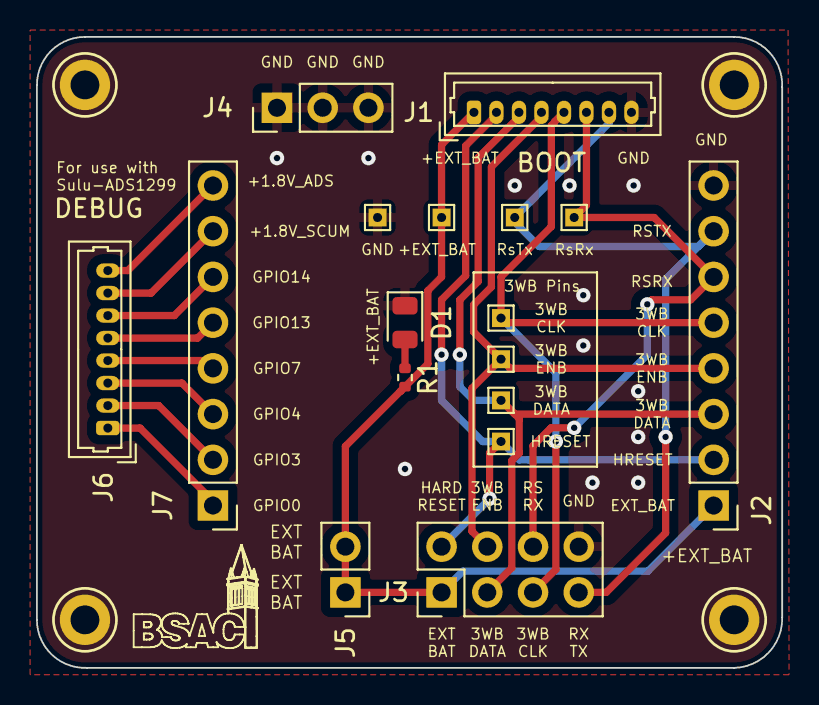
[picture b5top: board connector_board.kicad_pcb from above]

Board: 2 copper layers, 41.4 x 35.1 mm, 21 parts (0 on the bottom side), 17 nets.

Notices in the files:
parts and their libraries:
Copyright 2021 Accelerated Designs. All rights reserved.
